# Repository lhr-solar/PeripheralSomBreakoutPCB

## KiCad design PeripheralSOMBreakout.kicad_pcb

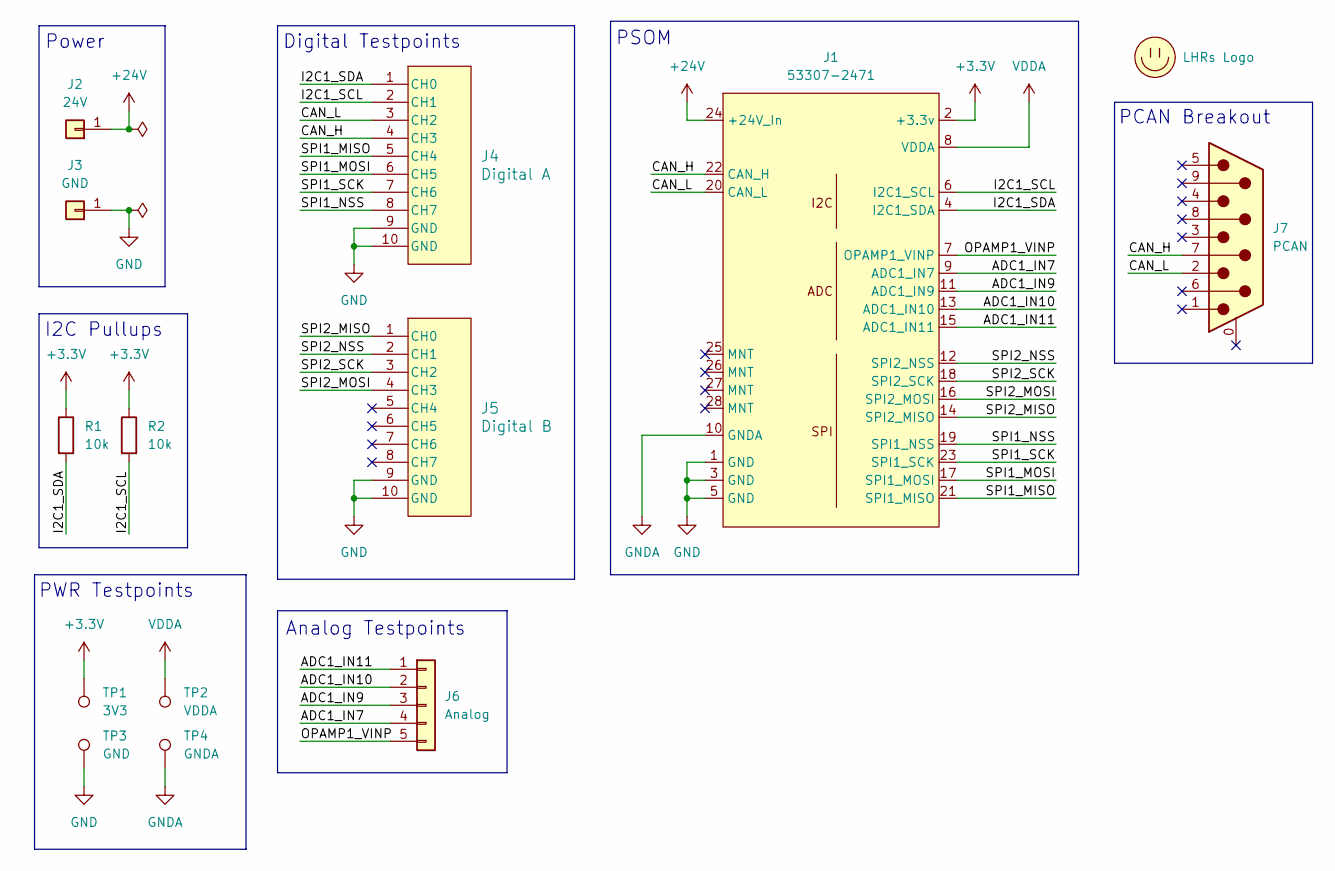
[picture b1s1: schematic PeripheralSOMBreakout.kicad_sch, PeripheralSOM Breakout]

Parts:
J1: 53307-2471; PeripheralSOM
J2: 24V; 5754
J3: GND; 5754
J4: Digital A; CONN_SFH11-xxxC-D05-ST-XX_SUL
J5: Digital B; CONN_SFH11-xxxC-D05-ST-XX_SUL
J6: Analog; PinHeader_1x05_P2.54mm_Vertical
J7: PCAN; AMPHENOL_L77SDE09SA4CH3R
LOGO1: LHRs Logo; LHRs_LOGO
R1, R2: 10k; R_0603_1608Metric_Pad0.98x0.95mm_HandSolder
TP1: 3V3; PinHeader_1x01_P2.54mm_Vertical
TP2: VDDA; PinHeader_1x01_P2.54mm_Vertical
TP3: GND; PinHeader_1x01_P2.54mm_Vertical
TP4: GNDA; PinHeader_1x01_P2.54mm_Vertical

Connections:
+3.3V: J1.2 (+3.3v), R1.1, R2.1, TP1.1
+24V: J1.24 (+24V_In), J2.1
/ADC1_IN7: J1.9 (ADC1_IN7), J6.4
/ADC1_IN9: J1.11 (ADC1_IN9), J6.3
/ADC1_IN10: J1.13 (ADC1_IN10), J6.2
/ADC1_IN11: J1.15 (ADC1_IN11), J6.1
/CAN_H: J1.22 (CAN_H), J4.4 (CH3), J7.7
/CAN_L: J1.20 (CAN_L), J4.3 (CH2), J7.2
/I2C1_SCL: J1.6 (I2C1_SCL), J4.2 (CH1), R2.2
/I2C1_SDA: J1.4 (I2C1_SDA), J4.1 (CH0), R1.2
/OPAMP1_VINP: J1.7 (OPAMP1_VINP), J6.5
/SPI1_MISO: J1.21 (SPI1_MISO), J4.5 (CH4)
/SPI1_MOSI: J1.17 (SPI1_MOSI), J4.6 (CH5)
/SPI1_NSS: J1.19 (SPI1_NSS), J4.8 (CH7)
/SPI1_SCK: J1.23 (SPI1_SCK), J4.7 (CH6)
/SPI2_MISO: J1.14 (SPI2_MISO), J5.1 (CH0)
/SPI2_MOSI: J1.16 (SPI2_MOSI), J5.4 (CH3)
/SPI2_NSS: J1.12 (SPI2_NSS), J5.2 (CH1)
/SPI2_SCK: J1.18 (SPI2_SCK), J5.3 (CH2)
GND: J1.1 (GND), J1.3 (GND), J1.5 (GND), J3.1, J4.9 (GND), J4.10 (GND), J5.9 (GND), J5.10 (GND), TP3.1
GNDA: J1.10 (GNDA), TP4.1
VDDA: J1.8 (VDDA), TP2.1

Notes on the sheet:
Digital Testpoints
Power
I2C Pullups
PCAN Breakout
PWR Testpoints
PSOM
Analog Testpoints

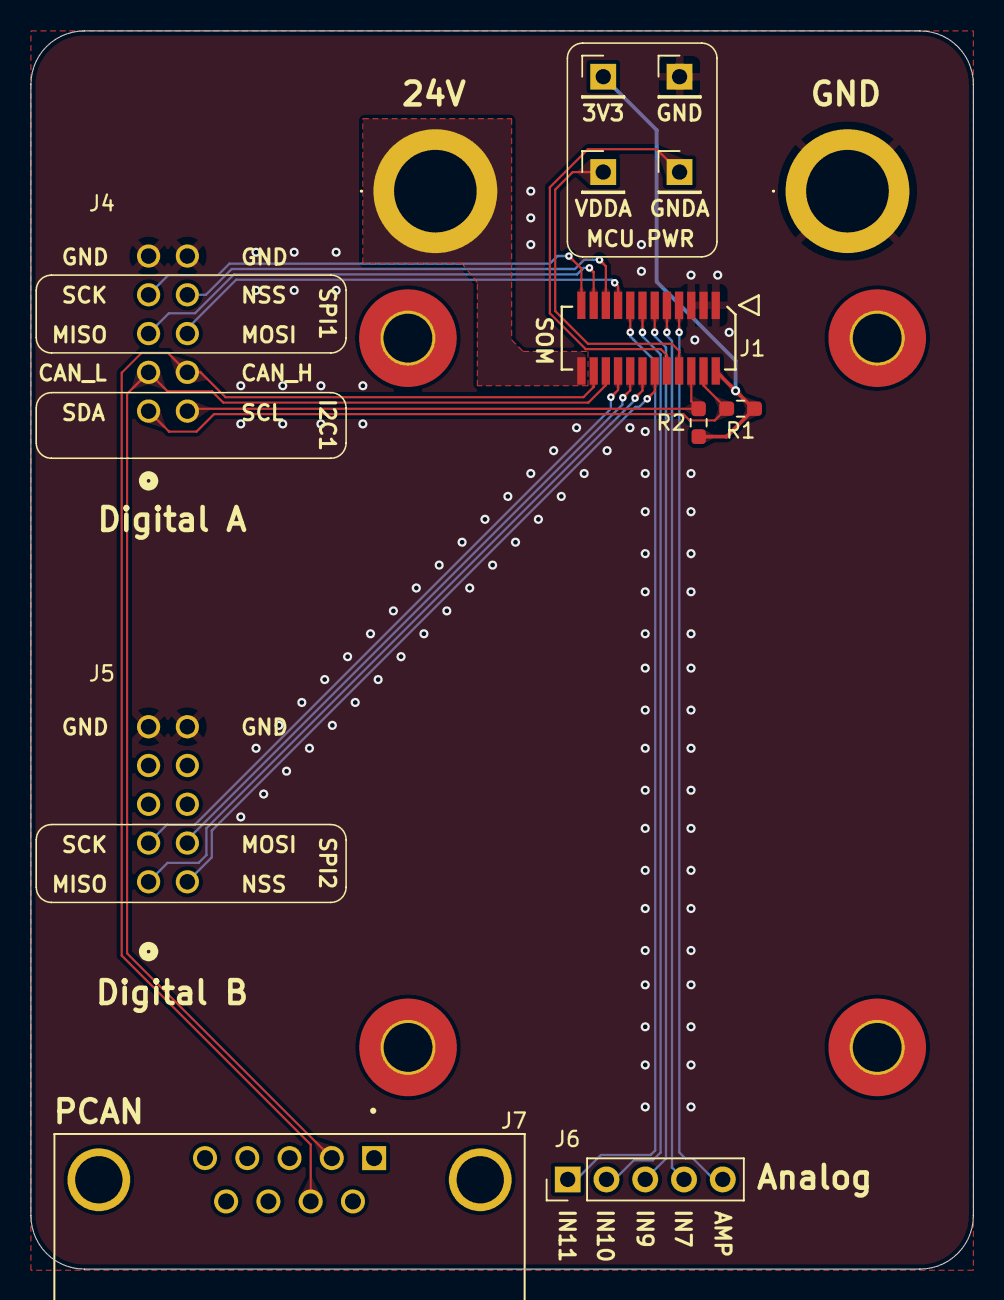
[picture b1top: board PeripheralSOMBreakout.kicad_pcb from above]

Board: 2 copper layers, 61.8 x 81.1 mm, 14 parts (0 on the bottom side), 22 nets.

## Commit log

2025-08-22 purge old files
2025-08-22 add kicad bild
2025-08-22 basic stuff
2025-08-23 finished
2025-08-23 stupid
2025-08-23 add db9 for can
2025-10-13 PSOM Breakout (#1)
    * purge old files
    * add kicad bild
    * basic stuff
    * finished
    * stupid
    * add db9 for can
